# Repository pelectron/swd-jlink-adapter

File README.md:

# swd-jlink-adapter
This repo contains a kicad project of a simple breakout board for JLinks to 10 and 20 pin JTAG/SWD connectors with 1.27 and 2.54 mm pitch.

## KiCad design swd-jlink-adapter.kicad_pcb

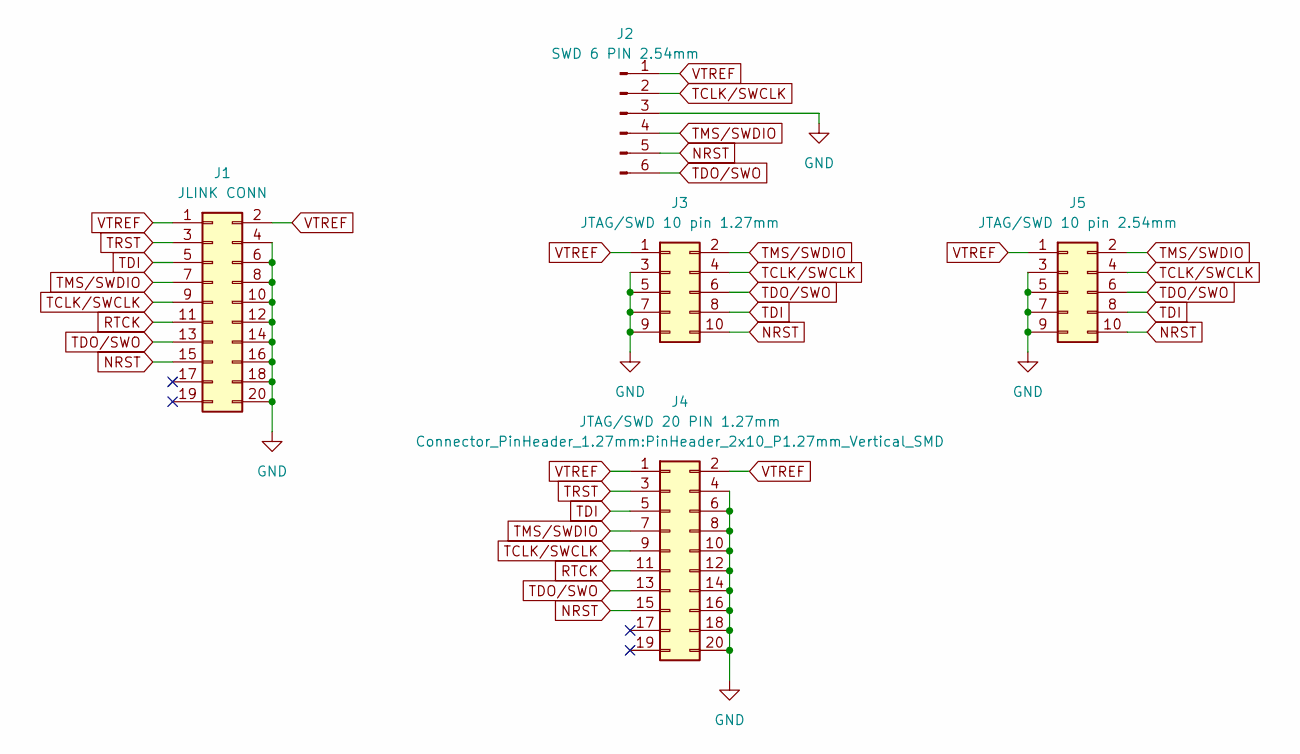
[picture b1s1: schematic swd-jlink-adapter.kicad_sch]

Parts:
J1: JLINK CONN; PinSocket_2x10_P2.54mm_Horizontal
J2: SWD 6 PIN 2.54mm; PinHeader_1x06_P2.54mm_Vertical
J3: JTAG/SWD 10 pin 1.27mm; PinHeader_2x05_P1.27mm_Vertical_SMD
J4: JTAG/SWD 20 PIN 1.27mm; PinHeader_2x10_P1.27mm_Vertical_SMD
J5: JTAG/SWD 10 pin 2.54mm; PinHeader_2x05_P2.54mm_Vertical

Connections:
GND: J1.4, J1.6, J1.8, J1.10, J1.12, J1.14, J1.16, J1.18, J1.20, J2.3, J3.3, J3.5, J3.7, J3.9, J4.4, J4.6, J4.8, J4.10, J4.12, J4.14, J4.16, J4.18, J4.20, J5.3, J5.5, J5.7, J5.9
NRST: J1.15, J2.5, J3.10, J4.15, J5.10
RTCK: J1.11, J4.11
TCLK/SWCLK: J1.9, J2.2, J3.4, J4.9, J5.4
TDI: J1.5, J3.8, J4.5, J5.8
TDO/SWO: J1.13, J2.6, J3.6, J4.13, J5.6
TMS/SWDIO: J1.7, J2.4, J3.2, J4.7, J5.2
TRST: J1.3, J4.3
VTREF: J1.1, J1.2, J2.1, J3.1, J4.1, J4.2, J5.1

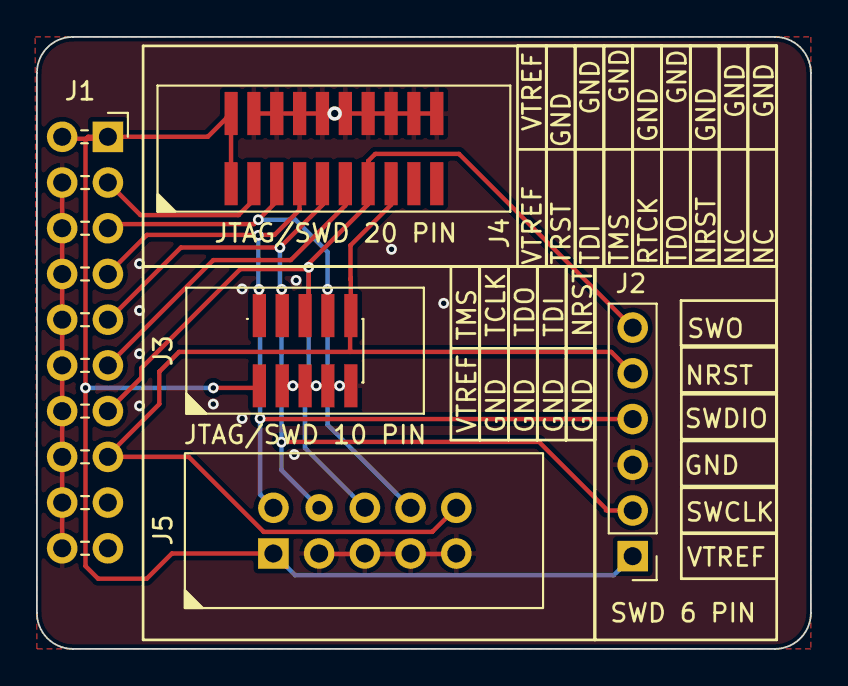
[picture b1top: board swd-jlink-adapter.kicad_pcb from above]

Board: 2 copper layers, 43.0 x 34.0 mm, 5 parts (0 on the bottom side), 9 nets.

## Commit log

2023-01-19 version 1
